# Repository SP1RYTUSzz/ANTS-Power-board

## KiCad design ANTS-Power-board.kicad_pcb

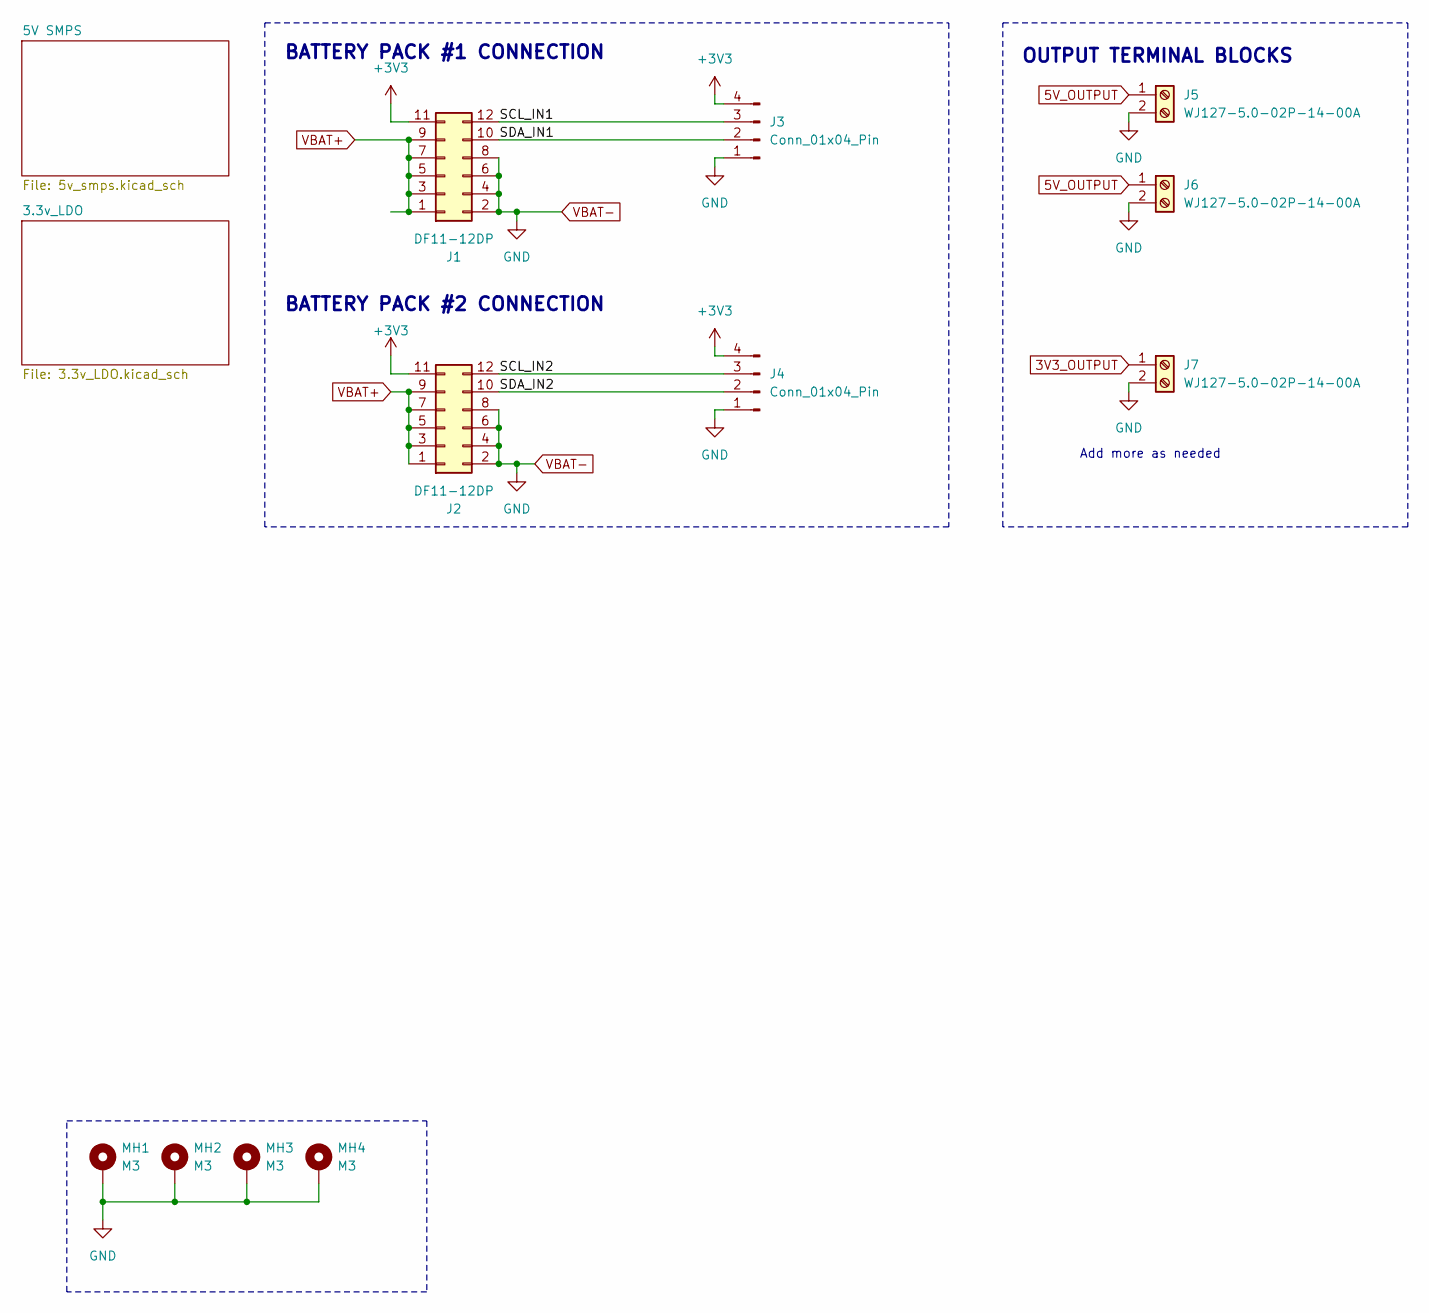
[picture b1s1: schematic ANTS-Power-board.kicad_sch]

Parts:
J1, J2: DF11-12DP; Hirose_DF11-12DP-2DSA_2x06_P2.00mm_Vertical; LCSC C506658
J3, J4: Conn_01x04_Pin; PinSocket_1x04_P2.54mm_Vertical
J5, J6, J7: WJ127-5.0-02P-14-00A; CONN-TH_MKDS1-2-3.5
MH1, MH2, MH3, MH4: M3; MountingHole_3.2mm_M3_Pad_Via

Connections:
3V3_OUTPUT: J7.1; also elsewhere on the board
5V_OUTPUT: J5.1, J6.1; also elsewhere on the board
+3V3: J1.11, J2.11, J3.4, J4.4
/SCL_IN1: J1.12, J3.3
/SCL_IN2: J2.12, J4.3
/SDA_IN1: J1.10, J3.2
/SDA_IN2: J2.10, J4.2
VBAT+: J1.1, J1.3, J1.5, J1.7, J1.9, J2.1, J2.3, J2.5, J2.7, J2.9; also elsewhere on the board
VBAT-: J1.2, J1.4, J1.6, J1.8, J2.2, J2.4, J2.6, J2.8, J3.1, J4.1, J5.2, J6.2, J7.2, MH1.1, MH2.1, MH3.1, MH4.1; also elsewhere on the board

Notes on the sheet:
OUTPUT TERMINAL BLOCKS
BATTERY PACK #2 CONNECTION
BATTERY PACK #1 CONNECTION
Add more as needed

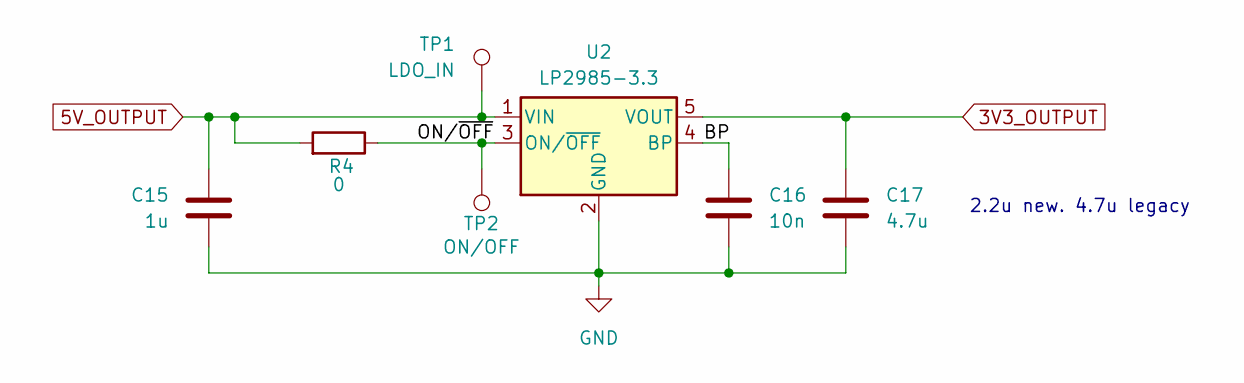
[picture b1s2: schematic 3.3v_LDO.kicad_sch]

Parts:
C15: 1u; C_0603_1608Metric; LCSC C15849
C16: 10n; C_0402_1005Metric; LCSC C15195
C17: 4.7u; C_0603_1608Metric; LCSC C19666
R4: 0; R_0603_1608Metric; LCSC C14709
TP1: LDO_IN; TestPoint_THTPad_D1.0mm_Drill0.5mm
TP2: ON/OFF; TestPoint_THTPad_D1.0mm_Drill0.5mm
U2: LP2985-3.3; SOT-23-5; LCSC C95414

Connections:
3V3_OUTPUT: C17.1, U2.5 (VOUT); also elsewhere on the board
5V_OUTPUT: C15.1, R4.2, TP1.1, U2.1 (VIN); also elsewhere on the board
/3.3v_LDO/BP: C16.1, U2.4 (BP)
/3.3v_LDO/ON/~OFF: R4.1, TP2.1, U2.3 (ON/~OFF)
VBAT-: C15.2, C16.2, C17.2, U2.2 (GND); also elsewhere on the board

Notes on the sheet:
2.2u new. 4.7u legacy

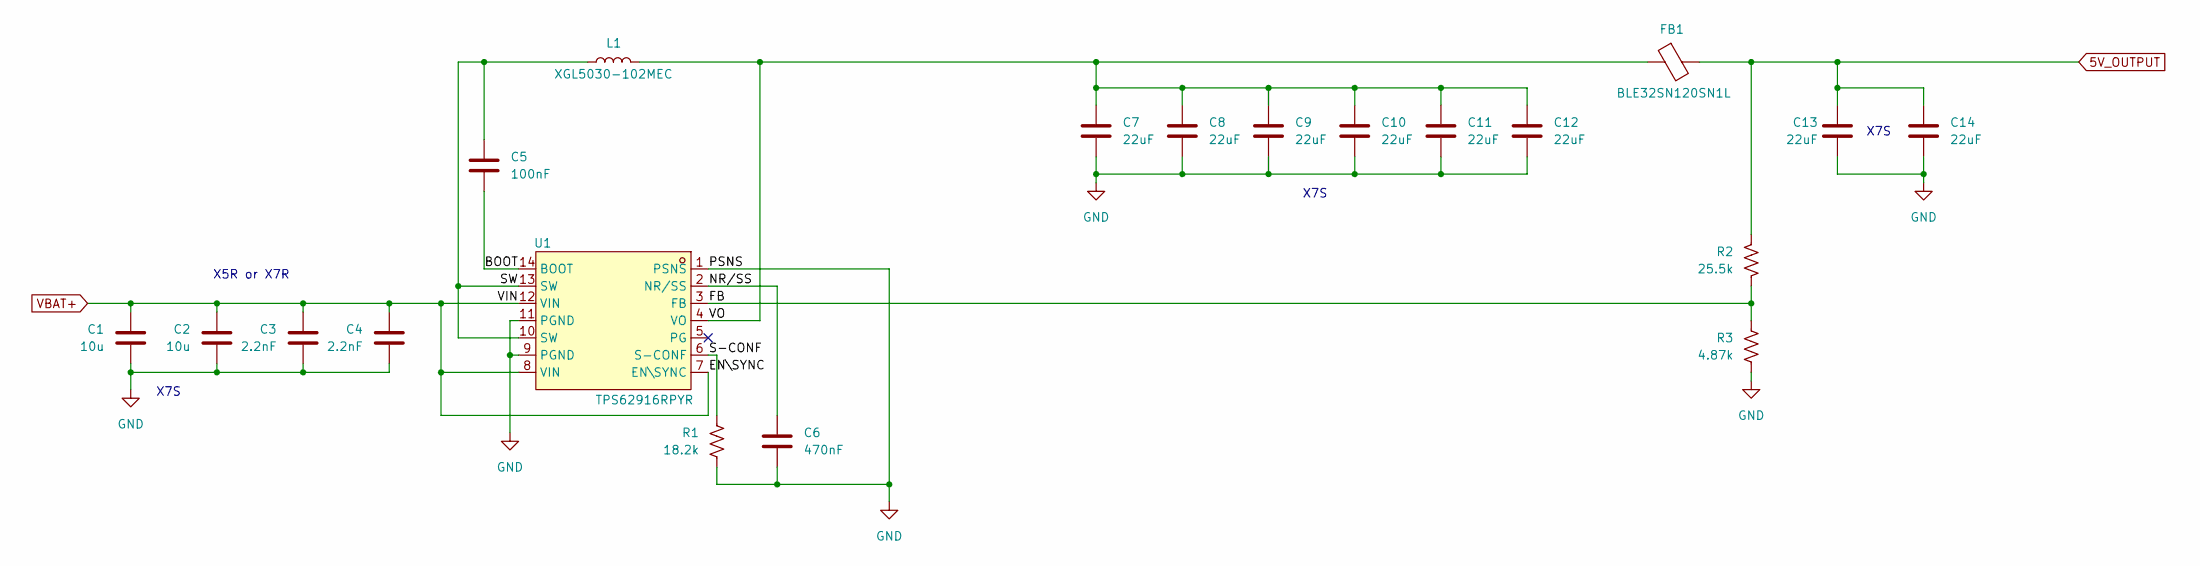
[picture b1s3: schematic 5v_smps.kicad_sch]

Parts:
C1, C2: 10u; C_0805_2012Metric; LCSC C15850
C3, C4: 2.2nF; C_0402_1005Metric; LCSC C84703
C5: 100nF; C_0402_1005Metric; LCSC C307331
C6: 470nF; C_0402_1005Metric
C7, C8, C9, C10, C11, C12, C13, C14: 22uF; C_0805_2012Metric; LCSC C45783
FB1: BLE32SN120SN1L; L_1210_3225Metric; LCSC C5597997
L1: XGL5030-102MEC; L_Coilcraft_XAL5030-XXX; LCSC C6937849
R1: 18.2k; R_0402_1005Metric; LCSC C2076827
R2: 25.5k; R_0402_1005Metric; LCSC C2076811
R3: 4.87k; R_0402_1005Metric; LCSC C103067
U1: TPS62916RPYR; VQFN-HR-14_L3.0-W2.5-P0.50-TL_TI_RPY; LCSC Part C32628642

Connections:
5V_OUTPUT: C13.1, C14.1, FB1.2, R2.1; also elsewhere on the board
/5V SMPS/BOOT: C5.2, U1.14 (BOOT)
/5V SMPS/FB: R2.2, R3.1, U1.3 (FB)
/5V SMPS/NR/SS: C6.1, U1.2 (NR/SS)
/5V SMPS/S-CONF: R1.1, U1.6 (S-CONF)
/5V SMPS/SW: C5.1, L1.1, U1.10 (SW), U1.13 (SW)
/5V SMPS/VO: C7.1, C8.1, C9.1, C10.1, C11.1, C12.1, FB1.1, L1.2, U1.4 (VO)
VBAT+: C1.1, C2.1, C3.1, C4.1, U1.7 (EN\SYNC), U1.8 (VIN), U1.12 (VIN); also elsewhere on the board
VBAT-: C1.2, C2.2, C3.2, C4.2, C6.2, C7.2, C8.2, C9.2, C10.2, C11.2, C12.2, C13.2, C14.2, R1.2, R3.2, U1.1 (PSNS), U1.9 (PGND), U1.11 (PGND); also elsewhere on the board

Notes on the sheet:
X7S
X5R or X7R

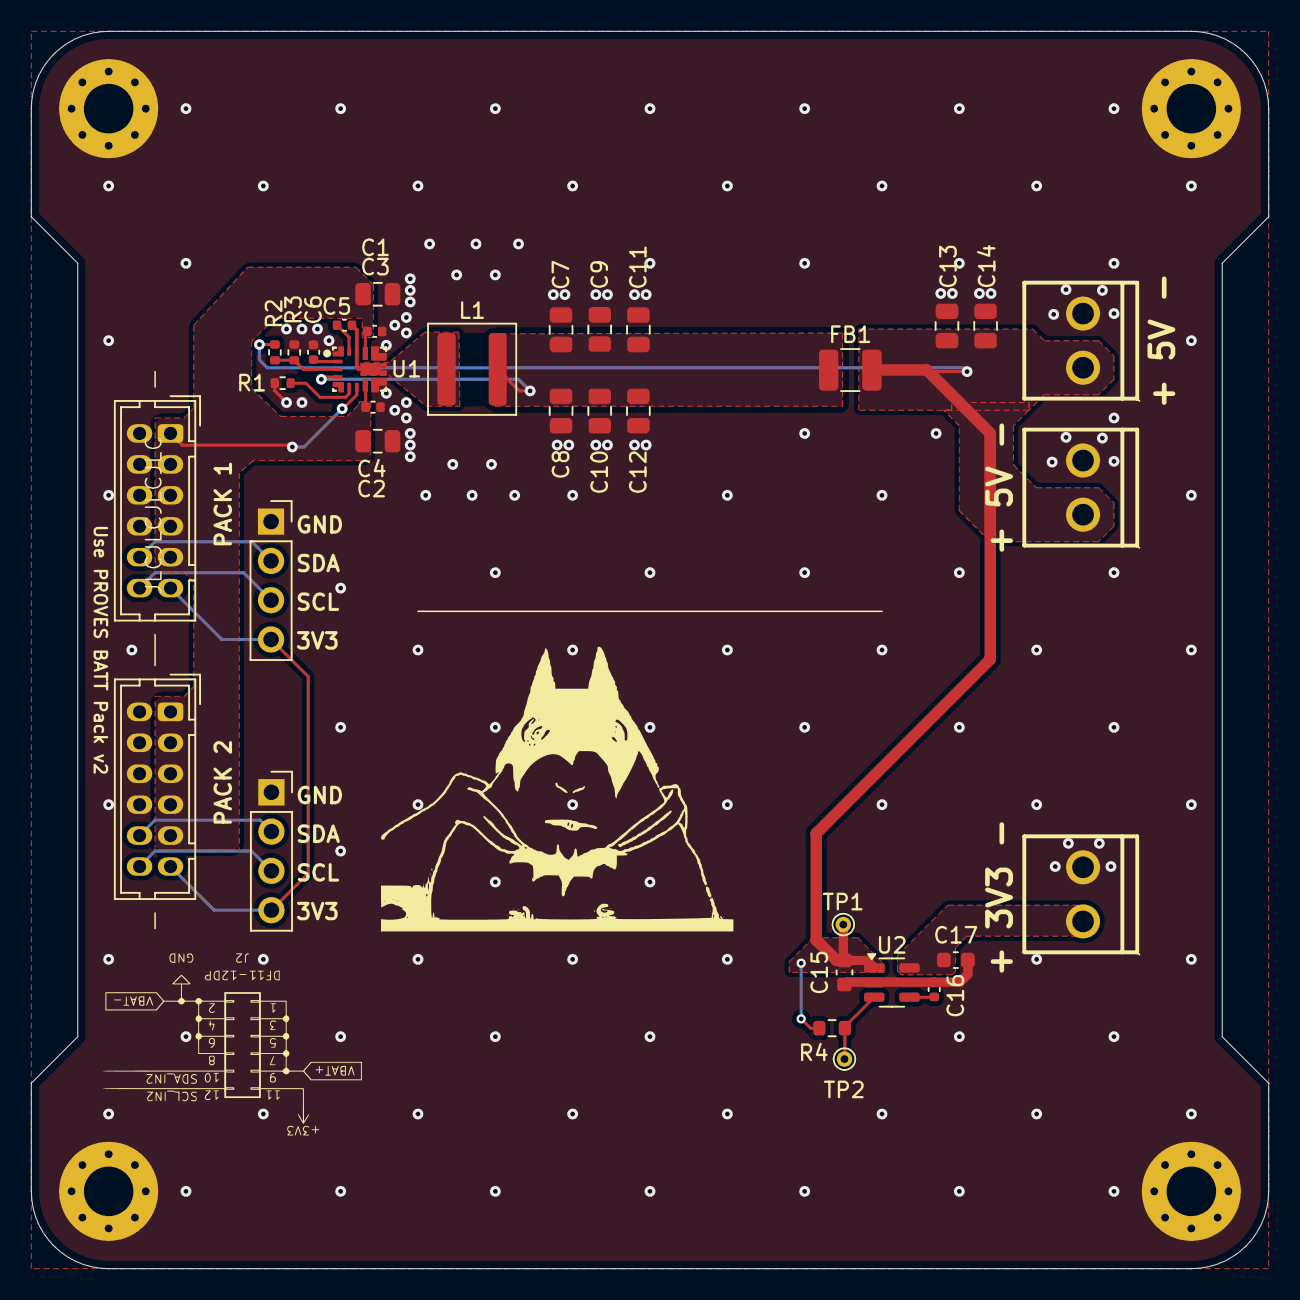
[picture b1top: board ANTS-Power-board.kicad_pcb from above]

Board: 2 copper layers, 80.0 x 80.0 mm, 38 parts (0 on the bottom side), 17 nets.

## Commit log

2026-03-28 Init Project Creation
2026-03-28 add capacitor
2026-03-28 Initial Project and Components creation
2026-03-31 updated smps
2026-03-31 Clean up SMPS schematic
2026-04-03 Schematic finished; PCB ready for basic layout
    Finished the ferrite bead footprint and setup the schematic for the PCB. Schematic has been portered over to the PCB Editor and is ready to start the basic parts layout. The PCB board is set up for t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
2026-04-03 Ross Added branch
    added a branch
2026-04-04 Wiring done; grounding and error checking still needs to be done
    Wiring done; everything still needs to be grounded, error checking, labeling on the board, and final stuff like that still need to be done
2026-04-06 add connections
2026-04-06 Import one DF11
2026-04-07 Add connectors & adjust board cuts
    - Add DF11 and ScrewTerminals
    - Add new edge cuts
2026-04-07 Ferrite bead labeling on PCB fixed
2026-04-07 Made some fill zones
2026-04-09 Did the changes that Tri asked
    Did the changes that Tri asked
    Labeling on board and some fixes on rule checker needed to be done.
2026-04-12 Add LDO schematic + layout
2026-04-12 Finished schematic & layout
2026-04-14 rewire LDO input to 5V from VBAT and verify DRC
2026-04-14 Add production files
2026-04-14 Adjust production files
2026-04-14 Add decoratives
2026-04-15 schematic for new DF11 and WJ127 connectors
2026-04-15 update to batt pack v2 (red). add screw terminal
2026-04-15 Add decorations
2026-04-15 Fix a LCSC# for resistor
